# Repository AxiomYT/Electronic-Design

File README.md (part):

# 70cm - 2M Diplexer

* Implements frequency-domain multiplexing. Two input ports (2M, 70CM) are multiplexed onto a third port (OUT)
* the signals on 2M and 70CKM can coexist on OUT port without interfering with each other.
* the signal on 2M Port will occupy the VHF Band and the signal on the 70CM will occupy the UHF band.
* the diplexer consists of a lowpass filter connecting 70CM Port and OUT 
* and a high pass filter connecting 2M Port and OUT.
## PCB

### Topside

### Rearside

## Wiring Diagram

<p>
  <meta http-equiv="content-type" content="text/html; charset=utf-8">
</p>
<p style="margin: 0px; padding: 0px; cursor: text; box-sizing: border-box; counter-reset: list-1 0 list-2 0 list-3 0 list-4 0 list-5 0 list-6 0 list-7 0 list-8 0 list-9 0; color: rgb(49, 49, 49); font-family: Helvetica, Arial, sans-serif; font-size: 13px; font-style: normal; font-variant-ligatures: normal; font-variant-caps: normal; font-weight: 400; letter-spacing: normal; orphans: 2; text-align: left; text-indent: 0px; text-transform: none; white-space: pre-wrap; widows: 2; word-spacing: 0px; -webkit-text-stroke-width: 0px; background-color: rgb(255, 255, 255); text-decoration-style: initial; text-decoration-color: initial;">I needed a small-ish collapsible Yagi-Uda antenna for portable use. Naturally I decided that if I was going to build one, I was going to do it right - the coolest Yagi on the block, the envy of the nearest ham-vention if you will</p>
<p style="margin: 0px; padding: 0px; cursor: text; box-sizing: border-box; counter-reset: list-1 0 list-2 0 list-3 0 list-4 0 list-5 0 list-6 0 list-7 0 list-8 0 list-9 0; color: rgb(49, 49, 49); font-family: Helvetica, Arial, sans-serif; font-size: 13px; font-style: normal; font-variant-ligatures: normal; font-variant-caps: normal; font-weight: 400; letter-spacing: normal; orphans: 2; text-align: left; text-indent: 0px; text-transform: none; white-space: pre-wrap; widows: 2; word-spacing: 0px; -webkit-text-stroke-width: 0px; background-color: rgb(255, 255, 255); text-decoration-style: initial; text-decoration-color: initial;">
  <br style="box-sizing: border-box;">
</p>
<p style="margin: 0px; padding: 0px; cursor: text; box-sizing: border-box; counter-reset: list-1 0 list-2 0 list-3 0 list-4 0 list-5 0 list-6 0 list-7 0 list-8 0 list-9 0; color: rgb(49, 49, 49); font-family: Helvetica, Arial, sans-serif; font-size: 13px; font-style: normal; font-variant-ligatures: normal; font-variant-caps: normal; font-weight: 400; letter-spacing: normal; orphans: 2; text-align: left; text-indent: 0px; text-transform: none; white-space: pre-wrap; widows: 2; word-spacing: 0px; -webkit-text-stroke-width: 0px; background-color: rgb(255, 255, 255); text-decoration-style: initial; text-decoration-color: initial;"><span class="ql-size-huge" style="box-sizing: border-box; font-size: 2.5em;">V/UHF Yagi Diplexer</span></p>
<p style="margin: 0px; padding: 0px; cursor: text; box-sizing: border-box; counter-reset: list-1 0 list-2 0 list-3 0 list-4 0 list-5 0 list-6 0 list-7 0 list-8 0 list-9 0; color: rgb(49, 49, 49); font-family: Helvetica, Arial, sans-serif; font-size: 13px; font-style: normal; font-variant-ligatures: normal; font-variant-caps: normal; font-weight: 400; letter-spacing: normal; orphans: 2; text-align: left; text-indent: 0px; text-transform: none; white-space: pre-wrap; widows: 2; word-spacing: 0px; -webkit-text-stroke-width: 0px; background-color: rgb(255, 255, 255); text-decoration-style: initial; text-decoration-color: initial;">
  <br style="box-sizing: border-box;">
</p>
<p style="margin: 0px; padding: 0px; cursor: text; box-sizing: border-box; counter-reset: list-1 0 list-2 0 list-3 0 list-4 0 list-5 0 list-6 0 list-7 0 list-8 0 list-9 0; color: rgb(49, 49, 49); font-family: Helvetica, Arial, sans-serif; font-size: 13px; font-style: normal; font-variant-ligatures: normal; font-variant-caps: normal; font-weight: 400; letter-spacing: normal; orphans: 2; text-align: left; text-indent: 0px; text-transform: none; white-space: pre-wrap; widows: 2; word-spacing: 0px; -webkit-text-stroke-width: 0px; background-color: rgb(255, 255, 255); text-decoration-style: initial; text-decoration-color: initial;">I came across a project that utilised<em style="font-style: normal; box-sizing: border-box;">&nbsp;carbon fibre</em>, ( the coolest buzz word since blockchain) as a 2 Metre long lightweight boom - accompanied by 3D printed element holders and RG59 Matchingline ( more on that later )</p>
<p style="margin: 0px; padding: 0px; cursor: text; box-sizing: border-box; counter-reset: list-1 0 list-2 0 list-3 0 list-4 0 list-5 0 list-6 0 list-7 0 list-8 0 list-9 0; color: rgb(49, 49, 49); font-family: Helvetica, Arial, sans-serif; font-size: 13px; font-style: normal; font-variant-ligatures: normal; font-variant-caps: normal; font-weight: 400; letter-spacing: normal; orphans: 2; text-align: left; text-indent: 0px; text-transform: none; white-space: pre-wrap; widows: 2; word-spacing: 0px; -webkit-text-stroke-width: 0px; background-color: rgb(255, 255, 255); text-decoration-style: initial; text-decoration-color: initial;">
  <br style="box-sizing: border-box;">
</p>
<p style="margin: 0px; padding: 0px; cursor: text; box-sizing: border-box; counter-reset: list-1 0 list-2 0 list-3 0 list-4 0 list-5 0 list-6 0 list-7 0 list-8 0 list-9 0; color: rgb(49, 49, 49); font-family: Helvetica, Arial, sans-serif; font-size: 13px; font-style: normal; font-variant-ligatures: normal; font-variant-caps: normal; font-weight: 400; letter-spacing: normal; orphans: 2; text-align: left; text-indent: 0px; text-transform: none; white-space: pre-wrap; widows: 2; word-spacing: 0px; -webkit-text-stroke-width: 0px; background-color: rgb(255, 255, 255); text-decoration-style: initial; text-decoration-color: initial;">This project was hosted on Tysonpower.de (
  <a href="https://tysonpower.de/blog/carbon-arrow-yagi-antenna" style="text-decoration: underline; color: rgb(0, 102, 204); transition: color 0.25s ease-out 0s; box-sizing: border-box;" target="_blank">https://tysonpower.de/blog/carbon-arrow-yagi-antenna</a>)
</p>
<p style="margin: 0px; padding: 0px; cursor: text; box-sizing: border-box; counter-reset: list-1 0 list-2 0 list-3 0 list-4 0 list-5 0 list-6 0 list-7 0 list-8 0 list-9 0; color: rgb(49, 49, 49); font-family: Helvetica, Arial, sans-serif; font-size: 13px; font-style: normal; font-variant-ligatures: normal; font-variant-caps: normal; font-weight: 400; letter-spacing: normal; orphans: 2; text-align: left; text-indent: 0px; text-transform: none; white-space: pre-wrap; widows: 2; word-spacing: 0px; -webkit-text-stroke-width: 0px; background-color: rgb(255, 255, 255); text-decoration-style: initial; text-decoration-color: initial;">
  <br style="box-sizing: border-box;">
</p>
<p style="margin: 0px; padding: 0px; cursor: text; box-sizing: border-box; counter-reset: list-1 0 list-2 0 list-3 0 list-4 0 list-5 0 list-6 0 list-7 0 list-8 0 list-9 0; color: rgb(49, 49, 49); font-family: Helvetica, Arial, sans-serif; font-size: 13px; font-style: normal; font-variant-ligatures: normal; font-variant-caps: normal; font-weight: 400; letter-spacing: normal; orphans: 2; text-align: left; text-indent: 0px; text-transform: none; white-space: pre-wrap; widows: 2; word-spacing: 0px; -webkit-text-stroke-width: 0px; background-color: rgb(255, 255, 255); text-decoration-style: initial; text-decoration-color: initial;"><span style="box-sizing: border-box; color: rgb(0, 0, 0);">The Antenna has enough gain for use with a low power 5w handheld radio and is relatively light. This makes it perfect for my use case</span></p>
<p style="margin: 0px; padding: 0px; cursor: text; box-sizing: border-box; counter-reset: list-1 0 list-2 0 list-3 0 list-4 0 list-5 0 list-6 0 list-7 0 list-8 0 list-9 0; color: rgb(49, 49, 49); font-family: Helvetica, Arial, sans-serif; font-size: 13px; font-style: normal; font-variant-ligatures: normal; font-variant-caps: normal; font-weight: 400; letter-spacing: normal; orphans: 2; text-align: left; text-indent: 0px; text-transform: none; white-space: pre-wrap; widows: 2; word-spacing: 0px; -webkit-text-stroke-width: 0px; background-color: rgb(255, 255, 255); text-decoration-style: initial; text-decoration-color: initial;">
  <br style="box-sizing: border-box;">
</p>
<p style="margin: 0px; padding: 0px; cursor: text; box-sizing: border-box; counter-reset: list-1 0 list-2 0 list-3 0 list-4 0 list-5 0 list-6 0 list-7 0 list-8 0 list-9 0; color: rgb(49, 49, 49); font-family: Helvetica, Arial, sans-serif; font-size: 13px; font-style: normal; font-variant-ligatures: normal; font-variant-caps: normal; font-weight: 400; letter-spacing: normal; orphans: 2; text-align: left; text-indent: 0px; text-transform: none; white-space: pre-wrap; widows: 2; word-spacing: 0px; -webkit-text-stroke-width: 0px; background-color: rgb(255, 255, 255); text-decoration-style: initial; text-decoration-color: initial;"><strong style="box-sizing: border-box;">Material list</strong></p>
<p style="margin: 0px; padding: 0px; cursor: text; box-sizing: border-box; counter-reset: list-1 0 list-2 0 list-3 0 list-4 0 list-5 0 list-6 0 list-7 0 list-8 0 list-9 0; color: rgb(49, 49, 49); font-family: Helvetica, Arial, sans-serif; font-size: 13px; font-style: normal; font-variant-ligatures: normal; font-variant-caps: normal; font-weight: 400; letter-spacing: normal; orphans: 2; text-align: left; text-indent: 0px; text-transform: none; white-space: pre-wrap; widows: 2; word-spacing: 0px; -webkit-text-stroke-width: 0px; background-color: rgb(255, 255, 255); text-decoration-style: initial; text-decoration-color: initial;">
  <br style="box-sizing: border-box;">
</p>
<ul style="margin: 0px; padding: 0px 0px 0px 1.5em; list-style: none outside none; cursor: text; box-sizing: border-box; counter-reset: list-1 0 list-2 0 list-3 0 list-4 0 list-5 0 list-6 0 list-7 0 list-8 0 list-9 0; color: rgb(49, 49, 49); font-family: Helvetica, Arial, sans-serif; font-size: 13px; font-style: normal; font-variant-ligatures: normal; font-variant-caps: normal; font-weight: 400; letter-spacing: normal; orphans: 2; text-align: left; text-indent: 0px; text-transform: none; white-space: pre-wrap; widows: 2; word-spacing: 0px; -webkit-text-stroke-width: 0px; background-color: rgb(255, 255, 255); text-decoration-style: initial; text-decoration-color: initial;">
  <li style="margin: 0px; padding: 0px 0px 0px 1.5em; list-style: none outside none; box-sizing: border-box;">2x 50cm carbon rod - 12mm outer diameter (boom)</li>
  <li style="margin: 0px; padding: 0px 0px 0px 1.5em; list-style: none outside none; box-sizing: border-box;">Aluminium clamps for the carbon rods</li>
  <li style="margin: 0px; padding: 0px 0px 0px 1.5em; list-style: none outside none; box-sizing: border-box;">some m3 bolts and nuts</li>
  <li style="margin: 0px; padding: 0px 0px 0px 1.5em; list-style: none outside none; box-sizing: border-box;">3D printed parts - 
    <a href="https://www.thingiverse.com/thing:3289189" style="text-decoration: underline; color: rgb(0, 102, 204); transition: color 0.25s ease-out 0s; box-sizing: border-box;" target="_blank">https://www.thingiverse.com/thing:3289189</a>
  </li>
  <li style="margin: 0px; padding: 0px 0px 0px 1.5em; list-style: none outside none; box-sizing: border-box;">Aluminium rods with 6mm (~3,5m) and 10mm (~1,5m) diameter (Elements)</li>
  <li style="margin: 0px; padding: 0px 0px 0px 1.5em; list-style: none outside none; box-sizing: border-box;">50Ohm [ RG58/U ] and 75Ohm cable [ RG59 ] (at least two metres of each)</li>
  <li style="margin: 0px; padding: 0px 0px 0px 1.5em; list-style: none outside none; box-sizing: border-box;">Cable lugs (for m3 screws)</li>
</ul>
<p style="margin: 0px; padding: 0px; cursor: text; box-sizing: border-box; counter-reset: list-1 0 list-2 0 list-3 0 list-4 0 list-5 0 list-6 0 list-7 0 list-8 0 list-9 0; color: rgb(49, 49, 49); font-family: Helvetica, Arial, sans-serif; font-size: 13px; font-style: normal; font-variant-ligatures: normal; font-variant-caps: normal; font-weight: 400; letter-spacing: normal; orphans: 2; text-align: left; text-indent: 0px; text-transform: none; white-space: pre-wrap; widows: 2; word-spacing: 0px; -webkit-text-stroke-width: 0px; background-color: rgb(255, 255, 255); text-decoration-style: initial; text-decoration-color: initial;">
  <br style="box-sizing: border-box;">
</p>
<p style="margin: 0px; padding: 0px; cursor: text; box-sizing: border-box; counter-reset: list-1 0 list-2 0 list-3 0 list-4 0 list-5 0 list-6 0 list-7 0 list-8 0 list-9 0; color: rgb(49, 49, 49); font-family: Helvetica, Arial, sans-serif; font-size: 13px; font-style: normal; font-variant-ligatures: normal; font-variant-caps: normal; font-weight: 400; letter-spacing: normal; orphans: 2; text-align: left; text-indent: 0px; text-transform: none; white-space: pre-wrap; widows: 2; word-spacing: 0px; -webkit-text-stroke-width: 0px; background-color: rgb(255, 255, 255); text-decoration-style: initial; text-decoration-color: initial;"><span style="box-sizing: border-box; color: rgb(0, 0, 0);">The parts have to be spaced according to the image below to get the right spacing between the elements. Note that the 2m and 70cm yagi are crossed by 90°.</span></p>
<p style="margin: 0px; padding: 0px; cursor: text; box-sizing: border-box; counter-reset: list-1 0 list-2 0 list-3 0 list-4 0 list-5 0 list-6 0 list-7 0 list-8 0 list-9 0; color: rgb(49, 49, 49); font-family: Helvetica, Arial, sans-serif; font-size: 13px; font-style: normal; font-variant-ligatures: normal; font-variant-caps: normal; font-weight: 400; letter-spacing: normal; orphans: 2; text-align: left; text-indent: 0px; text-transform: none; white-space: pre-wrap; widows: 2; word-spacing: 0px; -webkit-text-stroke-width: 0px; background-color: rgb(255, 255, 255); text-decoration-style: initial; text-decoration-color: initial;">
  <br style="box-sizing: border-box;">
</p>
<p style="margin: 0px; padding: 0px; cursor: text; box-sizing: border-box; counter-reset: list-1 0 list-2 0 list-3 0 list-4 0 list-5 0 list-6 0 list-7 0 list-8 0 list-9 0; color: rgb(49, 49, 49); font-family: Helvetica, Arial, sans-serif; font-size: 13px; font-style: normal; font-variant-ligatures: normal; font-variant-caps: normal; font-weight: 400; letter-spacing: normal; orphans: 2; text-align: left; text-indent: 0px; text-transform: none; white-space: pre-wrap; widows: 2; word-spacing: 0px; -webkit-text-stroke-width: 0px; background-color: rgb(255, 255, 255); text-decoration-style: initial; text-decoration-color: initial;">
  
</p>
<p style="margin: 0px; padding: 0px; cursor: text; box-sizing: border-box; counter-reset: list-1 0 list-2 0 list-3 0 list-4 0 list-5 0 list-6 0 list-7 0 list-8 0 list-9 0; color: rgb(49, 49, 49); font-family: Helvetica, Arial, sans-serif; font-size: 13px; font-style: normal; font-variant-ligatures: normal; font-variant-caps: normal; font-weight: 400; letter-spacing: normal; orphans: 2; text-align: left; text-indent: 0px; text-transform: none; white-space: pre-wrap; widows: 2; word-spacing: 0px; -webkit-text-stroke-width: 0px; background-color: rgb(255, 255, 255); text-decoration-style: initial; text-decoration-color: initial;">
  <br style="box-sizing: border-box;">
</p>
<p style="margin: 0px; padding: 0px; cursor: text; box-sizing: border-box; counter-reset: list-1 0 list-2 0 list-3 0 list-4 0 list-5 0 list-6 0 list-7 0 list-8 0 list-9 0; color: rgb(49, 49, 49); font-family: Helvetica, Arial, sans-serif; font-size: 13px; font-style: normal; font-variant-ligatures: normal; font-variant-caps: normal; font-weight: 400; letter-spacing: normal; orphans: 2; text-align: left; text-indent: 0px; text-transform: none; white-space: pre-wrap; widows: 2; word-spacing: 0px; -webkit-text-stroke-width: 0px; background-color: rgb(255, 255, 255); text-decoration-style: initial; text-decoration-color: initial;"><span style="box-sizing: border-box; color: rgb(0, 0, 0);">The Elements need to have the following lengths and need to be mounted centred on the boom.</span></p>
<p style="margin: 0px; padding: 0px; cursor: text; box-sizing: border-box; counter-reset: list-1 0 list-2 0 list-3 0 list-4 0 list-5 0 list-6 0 list-7 0 list-8 0 list-9 0; color: rgb(49, 49, 49); font-family: Helvetica, Arial, sans-serif; font-size: 13px; font-style: normal; font-variant-ligatures: normal; font-variant-caps: normal; font-weight: 400; letter-spacing: normal; orphans: 2; text-align: left; text-indent: 0px; text-transform: none; white-space: pre-wrap; widows: 2; word-spacing: 0px; -webkit-text-stroke-width: 0px; background-color: rgb(255, 255, 255); text-decoration-style: initial; text-decoration-color: initial;">
  <br style="box-sizing: border-box;">
</p>
<p style="margin: 0px; padding: 0px; cursor: text; box-sizing: border-box; counter-reset: list-1 0 list-2 0 list-3 0 list-4 0 list-5 0 list-6 0 list-7 0 list-8 0 list-9 0; color: rgb(49, 49, 49); font-family: Helvetica, Arial, sans-serif; font-size: 13px; font-style: normal; font-variant-ligatures: normal; font-variant-caps: normal; font-weight: 400; letter-spacing: normal; orphans: 2; text-align: left; text-indent: 0px; text-transform: none; white-space: pre-wrap; widows: 2; word-spacing: 0px; -webkit-text-stroke-width: 0px; background-color: rgb(255, 255, 255); text-decoration-style: initial; text-decoration-color: initial;">
  
</p>
<p style="margin: 0px; padding: 0px; cursor: text; box-sizing: border-box; counter-reset: list-1 0 list-2 0 list-3 0 list-4 0 list-5 0 list-6 0 list-7 0 list-8 0 list-9 0; color: rgb(49, 49, 49); font-family: Helvetica, Arial, sans-serif; font-size: 13px; font-style: normal; font-variant-ligatures: normal; font-variant-caps: normal; font-weight: 400; letter-spacing: normal; orphans: 2; text-align: left; text-indent: 0px; text-transform: none; white-space: pre-wrap; widows: 2; word-spacing: 0px; -webkit-text-stroke-width: 0px; background-color: rgb(255, 255, 255); text-decoration-style: initial; text-decoration-color: initial;">
  <br style="box-sizing: border-box;">
</p>
<p style="margin: 0px; padding: 0px; cursor: text; box-sizing: border-box; counter-reset: list-1 0 list-2 0 list-3 0 list-4 0 list-5 0 list-6 0 list-7 0 list-8 0 list-9 0; color: rgb(49, 49, 49); font-family: Helvetica, Arial, sans-serif; font-size: 13px; font-style: normal; font-variant-ligatures: normal; font-variant-caps: normal; font-weight: 400; letter-spacing: normal; orphans: 2; text-align: left; text-indent: 0px; text-transform: none; white-space: pre-wrap; widows: 2; word-spacing: 0px; -webkit-text-stroke-width: 0px; background-color: rgb(255, 255, 255); text-decoration-style: initial; text-decoration-color: initial;">
  
</p>
<p style="margin: 0px; padding: 0px; cursor: text; box-sizing: border-box; counter-reset: list-1 0 list-2 0 list-3 0 list-4 0 list-5 0 list-6 0 list-7 0 list-8 0 list-9 0; color: rgb(49, 49, 49); font-family: Helvetica, Arial, sans-serif; font-size: 13px; font-style: normal; font-variant-ligatures: normal; font-variant-caps: normal; font-weight: 400; letter-spacing: normal; orphans: 2; text-align: left; text-indent: 0px; text-transform: none; white-space: pre-wrap; widows: 2; word-spacing: 0px; -webkit-text-stroke-width: 0px; background-color: rgb(255, 255, 255); text-decoration-style: initial; text-decoration-color: initial;">
  <br style="box-sizing: border-box;">
</p>
<p style="margin: 0px; padding: 0px; cursor: text; box-sizing: border-box; counter-reset: list-1 0 list-2 0 list-3 0 list-4 0 list-5 0 list-6 0 list-7 0 list-8 0 list-9 0; color: rgb(49, 49, 49); font-family: Helvetica, Arial, sans-serif; font-size: 13px; font-style: normal; font-variant-ligatures: normal; font-variant-caps: normal; font-weight: 400; letter-spacing: normal; orphans: 2; text-align: left; text-indent: 0px; text-transform: none; white-space: pre-wrap; widows: 2; word-spacing: 0px; -webkit-text-stroke-width: 0px; background-color: rgb(255, 255, 255); text-decoration-style: initial; text-decoration-color: initial;">
  <br style="box-sizing: border-box;">
</p>
<p style="margin: 0px; padding: 0px; cursor: text; box-sizing: border-box; counter-reset: list-1 0 list-2 0 list-3 0 list-4 0 list-5 0 list-6 0 list-7 0 list-8 0 list-9 0; color: rgb(49, 49, 49); font-family: Helvetica, Arial, sans-serif; font-size: 13px; font-style: normal; font-variant-ligatures: normal; font-variant-caps: normal; font-weight: 400; letter-spacing: normal; orphans: 2; text-align: left; text-indent: 0px; text-transform: none; white-space: pre-wrap; widows: 2; word-spacing: 0px; -webkit-text-stroke-width: 0px; background-color: rgb(255, 255, 255); text-decoration-style: initial; text-decoration-color: initial;"><strong class="ql-size-large" style="box-sizing: border-box; font-size: 1.5em;">Note on Matchingline / RF Magic</strong></p>
<p style="margin: 0px; padding: 0px; cursor: text; box-sizing: border-box; counter-reset: list-1 0 list-2 0 list-3 0 list-4 0 list-5 0 list-6 0 list-7 0 list-8 0 list-9 0; color: rgb(49, 49, 49); font-family: Helvetica, Arial, sans-serif; font-size: 13px; font-style: normal; font-variant-ligatures: normal; font-variant-caps: normal; font-weight: 400; letter-spacing: normal; orphans: 2; text-align: left; text-indent: 0px; text-transform: none; white-space: pre-wrap; widows: 2; word-spacing: 0px; -webkit-text-stroke-width: 0px; background-color: rgb(255, 255, 255); text-decoration-style: initial; text-decoration-color: initial;">
  <br style="box-sizing: border-box;">
</p>
<p style="margin: 0px; padding: 0px; cursor: text; box-sizing: border-box; counter-reset: list-1 0 list-2 0 list-3 0 list-4 0 list-5 0 list-6 0 list-7 0 list-8 0 list-9 0; color: rgb(49, 49, 49); font-family: Helvetica, Arial, sans-serif; font-size: 13px; font-style: normal; font-variant-ligatures: normal; font-variant-caps: normal; font-weight: 400; letter-spacing: normal; orphans: 2; text-align: left; text-indent: 0px; text-transform: none; white-space: pre-wrap; widows: 2; word-spacing: 0px; -webkit-text-stroke-width: 0px; background-color: rgb(255, 255, 255); text-decoration-style: initial; text-decoration-color: initial;">So you might have noticed I mentioned 75Ohm Cable ( 2 Metres of the stuff )</p>
<p style="margin: 0px; padding: 0px; cursor: text; box-sizing: border-box; counter-reset: list-1 0 list-2 0 list-3 0 list-4 0 list-5 0 list-6 0 list-7 0 list-8 0 list-9 0; color: rgb(49, 49, 49); font-family: Helvetica, Arial, sans-serif; font-size: 13px; font-style: normal; font-variant-ligatures: normal; font-variant-caps: normal; font-weight: 400; letter-spacing: normal; orphans: 2; text-align: left; text-indent: 0px; text-transform: none; white-space: pre-wrap; widows: 2; word-spacing: 0px; -webkit-text-stroke-width: 0px; background-color: rgb(255, 255, 255); text-decoration-style: initial; text-decoration-color: initial;">
  <br style="box-sizing: border-box;">
</p>
<p style="margin: 0px; padding: 0px; cursor: text; box-sizing: border-box; counter-reset: list-1 0 list-2 0 list-3 0 list-4 0 list-5 0 list-6 0 list-7 0 list-8 0 list-9 0; color: rgb(49, 49, 49); font-family: Helvetica, Arial, sans-serif; font-size: 13px; font-style: normal; font-variant-ligatures: normal; font-variant-caps: normal; font-weight: 400; letter-spacing: normal; orphans: 2; text-align: left; text-indent: 0px; text-transform: none; white-space: pre-wrap; widows: 2; word-spacing: 0px; -webkit-text-stroke-width: 0px; background-color: rgb(255, 255, 255); text-decoration-style: initial; text-decoration-color: initial;">Your first step is to make a matchingline that is made out of two pieces of RG59 Concatenated and parallel to one another</p>
<p style="margin: 0px; padding: 0px; cursor: text; box-sizing: border-box; counter-reset: list-1 0 list-2 0 list-3 0 list-4 0 list-5 0 list-6 0 list-7 0 list-8 0 list-9 0; color: rgb(49, 49, 49); font-family: Helvetica, Arial, sans-serif; font-size: 13px; font-style: normal; font-variant-ligatures: normal; font-variant-caps: normal; font-weight: 400; letter-spacing: normal; orphans: 2; text-align: left; text-indent: 0px; text-transform: none; white-space: pre-wrap; widows: 2; word-spacing: 0px; -webkit-text-stroke-width: 0px; background-color: rgb(255, 255, 255); text-decoration-style: initial; text-decoration-color: initial;">
  <br style="box-sizing: border-box;">
</p>
<p style="margin: 0px; padding: 0px; cursor: text; box-sizing: border-box; counter-reset: list-1 0 list-2 0 list-3 0 list-4 0 list-5 0 list-6 0 list-7 0 list-8 0 list-9 0; color: rgb(49, 49, 49); font-family: Helvetica, Arial, sans-serif; font-size: 13px; font-style: normal; font-variant-ligatures: normal; font-variant-caps: normal; font-weight: 400; letter-spacing: normal; orphans: 2; text-align: left; text-indent: 0px; text-transform: none; white-space: pre-wrap; widows: 2; word-spacing: 0px; -webkit-text-stroke-width: 0px; background-color: rgb(255, 255, 255); text-decoration-style: initial; text-decoration-color: initial;">You will need two of these Cable harnesses -&nbsp;</p>
<p style="margin: 0px; padding: 0px; cursor: text; box-sizing: border-box; counter-reset: list-1 0 list-2 0 list-3 0 list-4 0 list-5 0 list-6 0 list-7 0 list-8 0 list-9 0; color: rgb(49, 49, 49); font-family: Helvetica, Arial, sans-serif; font-size: 13px; font-style: normal; font-variant-ligatures: normal; font-variant-caps: normal; font-weight: 400; letter-spacing: normal; orphans: 2; text-align: left; text-indent: 0px; text-transform: none; white-space: pre-wrap; widows: 2; word-spacing: 0px; -webkit-text-stroke-width: 0px; background-color: rgb(255, 255, 255); text-decoration-style: initial; text-decoration-color: initial;">one for the 2M Triple Element and one for the 70CM Penta-element</p>
<p style="margin: 0px; padding: 0px; cursor: text; box-sizing: border-box; counter-reset: list-1 0 list-2 0 list-3 0 list-4 0 list-5 0 list-6 0 list-7 0 list-8 0 list-9 0; color: rgb(49, 49, 49); font-family: Helvetica, Arial, sans-serif; font-size: 13px; font-style: normal; font-variant-ligatures: normal; font-variant-caps: normal; font-weight: 400; letter-spacing: normal; orphans: 2; text-align: left; text-indent: 0px; text-transform: none; white-space: pre-wrap; widows: 2; word-spacing: 0px; -webkit-text-stroke-width: 0px; background-color: rgb(255, 255, 255); text-decoration-style: initial; text-decoration-color: initial;">The length of the insulated part of the cable for the 2M band is 343mm and 115mm for the 70CM band</p>
<p style="margin: 0px; padding: 0px; cursor: text; box-sizing: border-box; counter-reset: list-1 0 list-2 0 list-3 0 list-4 0 list-5 0 list-6 0 list-7 0 list-8 0 list-9 0; color: rgb(49, 49, 49); font-family: Helvetica, Arial, sans-serif; font-size: 13px; font-style: normal; font-variant-ligatures: normal; font-variant-caps: normal; font-weight: 400; letter-spacing: normal; orphans: 2; text-align: left; text-indent: 0px; text-transform: none; white-space: pre-wrap; widows: 2; word-spacing: 0px; -webkit-text-stroke-width: 0px; background-color: rgb(255, 255, 255); text-decoration-style: initial; text-decoration-color: initial;">
  <br style="box-sizing: border-box;">
</p>
<p style="margin: 0px; padding: 0px; cursor: text; box-sizing: border-box; counter-reset: list-1 0 list-2 0 list-3 0 list-4 0 list-5 0 list-6 0 list-7 0 list-8 0 list-9 0; color: rgb(49, 49, 49); font-family: Helvetica, Arial, sans-serif; font-size: 13px; font-style: normal; font-variant-ligatures: normal; font-variant-caps: normal; font-weight: 400; letter-spacing: normal; orphans: 2; text-align: left; text-indent: 0px; text-transform: none; white-space: pre-wrap; widows: 2; word-spacing: 0px; -webkit-text-stroke-width: 0px; background-color: rgb(255, 255, 255); text-decoration-style: initial; text-decoration-color: initial;">I made sure that both stay parallel by using some isolating tape</p>
<p style="margin: 0px; padding: 0px; cursor: text; box-sizing: border-box; counter-reset: list-1 0 list-2 0 list-3 0 list-4 0 list-5 0 list-6 0 list-7 0 list-8 0 list-9 0; color: rgb(49, 49, 49); font-family: Helvetica, Arial, sans-serif; font-size: 13px; font-style: normal; font-variant-ligatures: normal; font-variant-caps: normal; font-weight: 400; letter-spacing: normal; orphans: 2; text-align: left; text-indent: 0px; text-transform: none; white-space: pre-wrap; widows: 2; word-spacing: 0px; -webkit-text-stroke-width: 0px; background-color: rgb(255, 255, 255); text-decoration-style: initial; text-decoration-color: initial;">To finish the cable - solder both the centre conductors together and the outer braiding of both parallel cables so you have one single signal and one single outer sheath connection on both sides.</p>
<p style="margin: 0px; padding: 0px; cursor: text; box-sizing: border-box; counter-reset: list-1 0 list-2 0 list-3 0 list-4 0 list-5 0 list-6 0 list-7 0 list-8 0 list-9 0; color: rgb(49, 49, 49); font-family: Helvetica, Arial, sans-serif; font-size: 13px; font-style: normal; font-variant-ligatures: normal; font-variant-caps: normal; font-weight: 400; letter-spacing: normal; orphans: 2; text-align: left; text-indent: 0px; text-transform: none; white-space: pre-wrap; widows: 2; word-spacing: 0px; -webkit-text-stroke-width: 0px; background-color: rgb(255, 255, 255); text-decoration-style: initial; text-decoration-color: initial;">
  <br style="box-sizing: border-box;">
</p>
<p style="margin: 0px; padding: 0px; cursor: text; box-sizing: border-box; counter-reset: list-1 0 list-2 0 list-3 0 list-4 0 list-5 0 list-6 0 list-7 0 list-8 0 list-9 0; color: rgb(49, 49, 49); font-family: Helvetica, Arial, sans-serif; font-size: 13px; font-style: normal; font-variant-ligatures: normal; font-variant-caps: normal; font-weight: 400; letter-spacing: normal; orphans: 2; text-align: left; text-indent: 0px; text-transform: none; white-space: pre-wrap; widows: 2; word-spacing: 0px; -webkit-text-stroke-width: 0px; background-color: rgb(255, 255, 255); text-decoration-style: initial; text-decoration-color: initial;">
  
</p>
<p style="margin: 0px; padding: 0px; cursor: text; box-sizing: border-box; counter-reset: list-1 0 list-2 0 list-3 0 list-4 0 list-5 0 list-6 0 list-7 0 list-8 0 list-9 0; color: rgb(49, 49, 49); font-family: Helvetica, Arial, sans-serif; font-size: 13px; font-style: normal; font-variant-ligatures: normal; font-variant-caps: normal; font-weight: 400; letter-spacing: normal; orphans: 2; text-align: left; text-indent: 0px; text-transform: none; white-space: pre-wrap; widows: 2; word-spacing: 0px; -webkit-text-stroke-width: 0px; background-color: rgb(255, 255, 255); text-decoration-style: initial; text-decoration-color: initial;">
  <br style="box-sizing: border-box;">
</p>
<p style="margin: 0px; padding: 0px; cursor: text; box-sizing: border-box; counter-reset: list-1 0 list-2 0 list-3 0 list-4 0 list-5 0 list-6 0 list-7 0 list-8 0 list-9 0; color: rgb(49, 49, 49); font-family: Helvetica, Arial, sans-serif; font-size: 13px; font-style: normal; font-variant-ligatures: normal; font-variant-caps: normal; font-weight: 400; letter-spacing: normal; orphans: 2; text-align: left; text-indent: 0px; text-transform: none; white-space: pre-wrap; widows: 2; word-spacing: 0px; -webkit-text-stroke-width: 0px; background-color: rgb(255, 255, 255); text-decoration-style: initial; text-decoration-color: initial;">For the output cable, use regular old RG58/U with your preferred termination (SMA / BNC)</p>
<p style="margin: 0px; padding: 0px; cursor: text; box-sizing: border-box; counter-reset: list-1 0 list-2 0 list-3 0 list-4 0 list-5 0 list-6 0 list-7 0 list-8 0 list-9 0; color: rgb(49, 49, 49); font-family: Helvetica, Arial, sans-serif; font-size: 13px; font-style: normal; font-variant-ligatures: normal; font-variant-caps: normal; font-weight: 400; letter-spacing: normal; orphans: 2; text-align: left; text-indent: 0px; text-transform: none; white-space: pre-wrap; widows: 2; word-spacing: 0px; -webkit-text-stroke-width: 0px; background-color: rgb(255, 255, 255); text-decoration-style: initial; text-decoration-color: initial;">
  <br style="box-sizing: border-box;">
</p>
<p style="margin: 0px; padding: 0px; cursor: text; box-sizing: border-box; counter-reset: list-1 0 list-2 0 list-3 0 list-4 0 list-5 0 list-6 0 list-7 0 list-8 0 list-9 0; color: rgb(49, 49, 49); font-family: Helvetica, Arial, sans-serif; font-size: 13px; font-style: normal; font-variant-ligatures: normal; font-variant-caps: normal; font-weight: 400; letter-spacing: normal; orphans: 2; text-align: left; text-indent: 0px; text-transform: none; white-space: pre-wrap; widows: 2; word-spacing: 0px; -webkit-text-stroke-width: 0px; background-color: rgb(255, 255, 255); text-decoration-style: initial; text-decoration-color: initial;">To connect to the elements to the feed point - I used Cable Lugs that get attached to the aluminium with screws.</p>
<p style="margin: 0px; padding: 0px; cursor: text; box-sizing: border-box; counter-reset: list-1 0 list-2 0 list-3 0 list-4 0 list-5 0 list-6 0 list-7 0 list-8 0 list-9 0; color: rgb(49, 49, 49); font-family: Helvetica, Arial, sans-serif; font-size: 13px; font-style: normal; font-variant-ligatures: normal; font-variant-caps: normal; font-weight: 400; letter-spacing: normal; orphans: 2; text-align: left; text-indent: 0px; text-transform: none; white-space: pre-wrap; widows: 2; word-spacing: 0px; -webkit-text-stroke-width: 0px; background-color: rgb(255, 255, 255); text-decoration-style: initial; text-decoration-color: initial;">
  <br style="box-sizing: border-box;">
</p>
<p style="margin: 0px; padding: 0px; cursor: text; box-sizing: border-box; counter-reset: list-1 0 list-2 0 list-3 0 list-4 0 list-5 0 list-6 0 list-7 0 list-8 0 list-9 0; color: rgb(49, 49, 49); font-family: Helvetica, Arial, sans-serif; font-size: 13px; font-style: normal; font-variant-ligatures: normal; font-variant-caps: normal; font-weight: 400; letter-spacing: normal; orphans: 2; text-align: left; text-indent: 0px; text-transform: none; white-space: pre-wrap; widows: 2; word-spacing: 0px; -webkit-text-stroke-width: 0px; background-color: rgb(255, 255, 255); text-decoration-style: initial; text-decoration-color: initial;">
  
</p>
<p style="margin: 0px; padding: 0px; cursor: text; box-sizing: border-box; counter-reset: list-1 0 list-2 0 list-3 0 list-4 0 list-5 0 list-6 0 list-7 0 list-8 0 list-9 0; color: rgb(49, 49, 49); font-family: Helvetica, Arial, sans-serif; font-size: 13px; font-style: normal; font-variant-ligatures: normal; font-variant-caps: normal; font-weight: 400; letter-spacing: normal; orphans: 2; text-align: left; text-indent: 0px; text-transform: none; white-space: pre-wrap; widows: 2; word-spacing: 0px; -webkit-text-stroke-width: 0px; background-color: rgb(255, 255, 255); text-decoration-style: initial; text-decoration-color: initial;">
  <br style="box-sizing: border-box;">
</p>
<p style="margin: 0px; padding: 0px; cursor: text; box-sizing: border-box; counter-reset: list-1 0 list-2 0 list-3 0 list-4 0 list-5 0 list-6 0 list-7 0 list-8 0 list-9 0; color: rgb(49, 49, 49); font-family: Helvetica, Arial, sans-serif; font-size: 13px; font-style: normal; font-variant-ligatures: normal; font-variant-caps: normal; font-weight: 400; letter-spacing: normal; orphans: 2; text-align: left; text-indent: 0px; text-transform: none; white-space: pre-wrap; widows: 2; word-spacing: 0px; -webkit-text-stroke-width: 0px; background-color: rgb(255, 255, 255); text-decoration-style: initial; text-decoration-color: initial;">
  <br style="box-sizing: border-box;">
</p>
<p style="margin: 0px; padding: 0px; cursor: text; box-sizing: border-box; counter-reset: list-1 0 list-2 0 list-3 0 list-4 0 list-5 0 list-6 0 list-7 0 list-8 0 list-9 0; color: rgb(49, 49, 49); font-family: Helvetica, Arial, sans-serif; font-size: 13px; font-style: normal; font-variant-ligatures: normal; font-variant-caps: normal; font-weight: 400; letter-spacing: normal; orphans: 2; text-align: left; text-indent: 0px; text-transform: none; white-space: pre-wrap; widows: 2; word-spacing: 0px; -webkit-text-stroke-width: 0px; background-color: rgb(255, 255, 255); text-decoration-style: initial; text-decoration-color: initial;"><strong class="ql-size-huge" style="box-sizing: border-box; font-size: 2.5em;">The PCB</strong></p>
<p style="margin: 0px; padding: 0px; cursor: text; box-sizing: border-box; counter-reset: list-1 0 list-2 0 list-3 0 list-4 0 list-5 0 list-6 0 list-7 0 list-8 0 list-9 0; color: rgb(49, 49, 49); font-family: Helvetica, Arial, sans-serif; font-size: 13px; font-style: normal; font-variant-ligatures: normal; font-variant-caps: normal; font-weight: 400; letter-spacing: normal; orphans: 2; text-align: left; text-indent: 0px; text-transform: none; white-space: pre-wrap; widows: 2; word-spacing: 0px; -webkit-text-stroke-width: 0px; background-color: rgb(255, 255, 255); text-decoration-style: initial; text-decoration-color: initial;">
  <br style="box-sizing: border-box;">
</p>
<p style="margin: 0px; padding: 0px; cursor: text; box-sizing: border-box; counter-reset: list-1 0 list-2 0 list-3 0 list-4 0 list-5 0 list-6 0 list-7 0 list-8 0 list-9 0; color: rgb(49, 49, 49); font-family: Helvetica, Arial, sans-serif; font-size: 13px; font-style: normal; font-variant-ligatures: normal; font-variant-caps: normal; font-weight: 400; letter-spacing: normal; orphans: 2; text-align: left; text-indent: 0px; text-transform: none; white-space: pre-wrap; widows: 2; word-spacing: 0px; -webkit-text-stroke-width: 0px; background-color: rgb(255, 255, 255); text-decoration-style: initial; text-decoration-color: initial;">Onto the reason for this post - The kind folks at PCBway reached out to me to help me print my circuit board design. This is a short outline of what it does!</p>
<p style="margin: 0px; padding: 0px; cursor: text; box-sizing: border-box; counter-reset: list-1 0 list-2 0 list-3 0 list-4 0 list-5 0 list-6 0 list-7 0 list-8 0 list-9 0; color: rgb(49, 49, 49); font-family: Helvetica, Arial, sans-serif; font-size: 13px; font-style: normal; font-variant-ligatures: normal; font-variant-caps: normal; font-weight: 400; letter-spacing: normal; orphans: 2; text-align: left; text-indent: 0px; text-transform: none; white-space: pre-wrap; widows: 2; word-spacing: 0px; -webkit-text-stroke-width: 0px; background-color: rgb(255, 255, 255); text-decoration-style: initial; text-decoration-color: initial;">
  <br style="box-sizing: border-box;">
</p>
<p style="margin: 0px; padding: 0px; cursor: text; box-sizing: border-box; counter-reset: list-1 0 list-2 0 list-3 0 list-4 0 list-5 0 list-6 0 list-7 0 list-8 0 list-9 0; color: rgb(49, 49, 49); font-family: Helvetica, Arial, sans-serif; font-size: 13px; font-style: normal; font-variant-ligatures: normal; font-variant-caps: normal; font-weight: 400; letter-spacing: normal; orphans: 2; text-align: left; text-indent: 0px; text-transform: none; white-space: pre-wrap; widows: 2; word-spacing: 0px; -webkit-text-stroke-width: 0px; background-color: rgb(255, 255, 255); text-decoration-style: initial; text-decoration-color: initial;">Because I only wanted one output to my radio - I added a diplexer, or otherwise known as RF Magic..for those interested - this is the theory behind diplexers</p>
<p style="margin: 0px; padding: 0px; cursor: text; box-sizing: border-box; counter-reset: list-1 0 list-2 0 list-3 0 list-4 0 list-5 0 list-6 0 list-7 0 list-8 0 list-9 0; color: rgb(49, 49, 49); font-family: Helvetica, Arial, sans-serif; font-size: 13px; font-style: normal; font-variant-ligatures: normal; font-variant-caps: normal; font-weight: 400; letter-spacing: normal; orphans: 2; text-align: left; text-indent: 0px; text-transform: none; white-space: pre-wrap; widows: 2; word-spacing: 0px; -webkit-text-stroke-width: 0px; background-color: rgb(255, 255, 255); text-decoration-style: initial; text-decoration-color: initial;">
  <br style="box-sizing: border-box;">
</p>
<ul style="margin: 0px; padding: 0px 0px 0px 1.5em; list-style: none outside none; cursor: text; box-sizing: border-box; counter-reset: list-1 0 list-2 0 list-3 0 list-4 0 list-5 0 list-6 0 list-7 0 list-8 0 list-9 0; color: rgb(49, 49, 49); font-family: Helvetica, Arial, sans-serif; font-size: 13px; font-style: normal; font-variant-ligatures: normal; font-variant-caps: normal; font-weight: 400; letter-spacing: normal; orphans: 2; text-align: left; text-indent: 0px; text-transform: none; white-space: pre-wrap; widows: 2; word-spacing: 0px; -webkit-text-stroke-width: 0px; background-color: rgb(255, 255, 255); text-decoration-style: initial; text-decoration-color: initial;">
  <li style="margin: 0px; padding: 0px 0px 0px 1.5em; list-style: none outside none; box-sizing: border-box;">Implements frequency-domain multiplexing. Two input ports (2M, 70CM) are multiplexed onto a third port (OUT)</li>
  <li style="margin: 0px; padding: 0px 0px 0px 1.5em; list-style: none outside none; box-sizing: border-box;">the signals on 2M and 70CM can coexist on OUT port without interfering with each other.</li>
  <li style="margin: 0px; padding: 0px 0px 0px 1.5em; list-style: none outside none; box-sizing: border-box;">the signal on 2M Port will occupy the VHF Band and the signal on the 70CM will occupy the UHF band.</li>
  <li style="margin: 0px; padding: 0px 0px 0px 1.5em; list-style: none outside none; box-sizing: border-box;">the diplexer consists of a lowpass filter connecting 70CM Port and OUT</li>
  <li style="margin: 0px; padding: 0px 0px 0px 1.5em; list-style: none outside none; box-sizing: border-box;">and a high pass filter connecting 2M Port and OUT.</li>
</ul>
<p style="margin: 0px; padding: 0px; cursor: text; box-sizing: border-box; counter-reset: list-1 0 list-2 0 list-3 0 list-4 0 list-5 0 list-6 0 list-7 0 list-8 0 list-9 0; color: rgb(49, 49, 49); font-family: Helvetica, Arial, sans-serif; font-size: 13px; font-style: normal; font-variant-ligatures: normal; font-variant-caps: normal; font-weight: 400; letter-spacing: normal; orphans: 2; text-align: left; text-indent: 0px; text-transform: none; white-space: pre-wrap; widows: 2; word-spacing: 0px; -webkit-text-stroke-width: 0px; background-color: rgb(255, 255, 255); text-decoration-style: initial; text-decoration-color: initial;">
  <br style="box-sizing: border-box;">
</p>
<p style="margin: 0px; padding: 0px; cursor: text; box-sizing: border-box; counter-reset: list-1 0 list-2 0 list-3 0 list-4 0 list-5 0 list-6 0 list-7 0 list-8 0 list-9 0; color: rgb(49, 49, 49); font-family: Helvetica, Arial, sans-serif; font-size: 13px; font-style: normal; font-variant-ligatures: normal; font-variant-caps: normal; font-weight: 400; letter-spacing: normal; orphans: 2; text-align: left; text-indent: 0px; text-transform: none; white-space: pre-wrap; widows: 2; word-spacing: 0px; -webkit-text-stroke-width: 0px; background-color: rgb(255, 255, 255); text-decoration-style: initial; text-decoration-color: initial;">This PCB can withstand roughly 10W ERP - which is 3 Watts more than any of my HT's can output. Plenty of breathing room + Gain.</p>
<p style="margin: 0px; padding: 0px; cursor: text; box-sizing: border-box; counter-reset: list-1 0 list-2 0 list-3 0 list-4 0 list-5 0 list-6 0 list-7 0 list-8 0 list-9 0; color: rgb(49, 49, 49); font-family: Helvetica, Arial, sans-serif; font-size: 13px; font-style: normal; font-variant-ligatures: normal; font-variant-caps: normal; font-weight: 400; letter-spacing: normal; orphans: 2; text-align: left; text-indent: 0px; text-transform: none; white-space: pre-wrap; widows: 2; word-spacing: 0px; -webkit-text-stroke-width: 0px; background-color: rgb(255, 255, 255); text-decoration-style: initial; text-decoration-color: initial;">
  <br style="box-sizing: border-box;">
</p>
<p style="margin: 0px; padding: 0px; cursor: text; box-sizing: border-box; counter-reset: list-1 0 list-2 0 list-3 0 list-4 0 list-5 0 list-6 0 list-7 0 list-8 0 list-9 0; color: rgb(49, 49, 49); font-family: Helvetica, Arial, sans-serif; font-size: 13px; font-style: normal; font-variant-ligatures: normal; font-variant-caps: normal; font-weight: 400; letter-spacing: normal; orphans: 2; text-align: left; text-indent: 0px; text-transform: none; white-space: pre-wrap; widows: 2; word-spacing: 0px; -webkit-text-stroke-width: 0px; background-color: rgb(255, 255, 255); text-decoration-style: initial; text-decoration-color: initial;">
  
</p>
<p style="margin: 0px; padding: 0px; cursor: text; box-sizing: border-box; counter-reset: list-1 0 list-2 0 list-3 0 list-4 0 list-5 0 list-6 0 list-7 0 list-8 0 list-9 0; color: rgb(49, 49, 49); font-family: Helvetica, Arial, sans-serif; font-size: 13px; font-style: normal; font-variant-ligatures: normal; font-variant-caps: normal; font-weight: 400; letter-spacing: normal; orphans: 2; text-align: left; text-indent: 0px; text-transform: none; white-space: pre-wrap; widows: 2; word-spacing: 0px; -webkit-text-stroke-width: 0px; background-color: rgb(255, 255, 255); text-decoration-style: initial; text-decoration-color: initial;">
  <br style="box-sizing: border-box;">
</p>
<h3 style="margin: 0px; padding: 0px; cursor: text; box-sizing: border-box; counter-reset: list-1 0 list-2 0 list-3 0 list-4 0 list-5 0 list-6 0 list-7 0 list-8 0 list-9 0; font-size: 1.17em; color: rgb(49, 49, 49); font-family: Helvetica, Arial, sans-serif; font-style: normal; font-variant-ligatures: normal; font-variant-caps: normal; letter-spacing: normal; orphans: 2; text-align: left; text-indent: 0px; text-transform: none; white-space: pre-wrap; widows: 2; word-spacing: 0px; -webkit-text-stroke-width: 0px; background-color: rgb(255, 255, 255); text-decoration-style: initial; text-decoration-color: initial;">Topside</h3>
<p style="margin: 0px; padding: 0px; cursor: text; box-sizing: border-box; counter-reset: list-1 0 list-2 0 list-3 0 list-4 0 list-5 0 list-6 0 list-7 0 list-8 0 list-9 0; color: rgb(49, 49, 49); font-family: Helvetica, Arial, sans-serif; font-size: 13px; font-style: normal; font-variant-ligatures: normal; font-variant-caps: normal; font-weight: 400; letter-spacing: normal; orphans: 2; text-align: left; text-indent: 0px; text-transform: none; white-space: pre-wrap; widows: 2; word-spacing: 0px; -webkit-text-stroke-width: 0px; background-color: rgb(255, 255, 255); text-decoration-style: initial; text-decoration-color: initial;">
  <br style="box-sizing: border-box;">
</p>
<p style="margin: 0px; padding: 0px; cursor: text; box-sizing: border-box; counter-reset: list-1 0 list-2 0 list-3 0 list-4 0 list-5 0 list-6 0 list-7 0 list-8 0 list-9 0; color: rgb(49, 49, 49); font-family: Helvetica, Arial, sans-serif; font-size: 13px; font-style: normal; font-variant-ligatures: normal; font-variant-caps: normal; font-weight: 400; letter-spacing: normal; orphans: 2; text-align: left; text-indent: 0px; text-transform: none; white-space: pre-wrap; widows: 2; word-spacing: 0px; -webkit-text-stroke-width: 0px; background-color: rgb(255, 255, 255); text-decoration-style: initial; text-decoration-color: initial;">
  
</p>
<p style="margin: 0px; padding: 0px; cursor: text; box-sizing: border-box; counter-reset: list-1 0 list-2 0 list-3 0 list-4 0 list-5 0 list-6 0 list-7 0 list-8 0 list-9 0; color: rgb(49, 49, 49); font-family: Helvetica, Arial, sans-serif; font-size: 13px; font-style: normal; font-variant-ligatures: normal; font-variant-caps: normal; font-weight: 400; letter-spacing: normal; orphans: 2; text-align: left; text-indent: 0px; text-transform: none; white-space: pre-wrap; widows: 2; word-spacing: 0px; -webkit-text-stroke-width: 0px; background-color: rgb(255, 255, 255); text-decoration-style: initial; text-decoration-color: initial;">
  <br style="box-sizing: border-box;">
</p>
<h3 style="margin: 0px; padding: 0px; cursor: text; box-sizing: border-box; counter-reset: list-1 0 list-2 0 list-3 0 list-4 0 list-5 0 list-6 0 list-7 0 list-8 0 list-9 0; font-size: 1.17em; color: rgb(49, 49, 49); font-family: Helvetica, Arial, sans-serif; font-style: normal; font-variant-ligatures: normal; font-variant-caps: normal; letter-spacing: normal; orphans: 2; text-align: left; text-indent: 0px; text-transform: none; white-space: pre-wrap; widows: 2; word-spacing: 0px; -webkit-text-stroke-width: 0px; background-color: rgb(255, 255, 255); text-decoration-style: initial; text-decoration-color: initial;">Rearside</h3>
<p style="margin: 0px; padding: 0px; cursor: text; box-sizing: border-box; counter-reset: list-1 0 list-2 0 list-3 0 list-4 0 list-5 0 list-6 0 list-7 0 list-8 0 list-9 0; color: rgb(49, 49, 49); font-family: Helvetica, Arial, sans-serif; font-size: 13px; font-style: normal; font-variant-ligatures: normal; font-variant-caps: normal; font-weight: 400; letter-spacing: normal; orphans: 2; text-align: left; text-indent: 0px; text-transform: none; white-space: pre-wrap; widows: 2; word-spacing: 0px; -webkit-text-stroke-width: 0px; background-color: rgb(255, 255, 255); text-decoration-style: initial; text-decoration-color: initial;">
  <br style="box-sizing: border-box;">
</p>
<p style="margin: 0px; padding: 0px; cursor: text; box-sizing: border-box; counter-reset: list-1 0 list-2 0 list-3 0 list-4 0 list-5 0 list-6 0 list-7 0 list-8 0 list-9 0; color: rgb(49, 49, 49); font-family: Helvetica, Arial, sans-serif; font-size: 13px; font-style: normal; font-variant-ligatures: normal; font-variant-caps: normal; font-weight: 400; letter-spacing: normal; orphans: 2; text-align: left; text-indent: 0px; text-transform: none; white-space: pre-wrap; widows: 2; word-spacing: 0px; -webkit-text-stroke-width: 0px; background-color: rgb(255, 255, 255); text-decoration-style: initial; text-decoration-color: initial;">
  
</p>
<p style="margin: 0px; padding: 0px; cursor: text; box-sizing: border-box; counter-reset: list-1 0 list-2 0 list-3 0 list-4 0 list-5 0 list-6 0 list-7 0 list-8 0 list-9 0; color: rgb(49, 49, 49); font-family: Helvetica, Arial, sans-serif; font-size: 13px; font-style: normal; font-variant-ligatures: normal; font-variant-caps: normal; font-weight: 400; letter-spacing: normal; orphans: 2; text-align: left; text-indent: 0px; text-transform: none; white-space: pre-wrap; widows: 2; word-spacing: 0px; -webkit-text-stroke-width: 0px; background-color: rgb(255, 255, 255); text-decoration-style: initial; text-decoration-color: initial;">
  <br style="box-sizing: border-box;">
</p>
<h2 style="margin: 0px; padding: 0px; cursor: text; box-sizing: border-box; counter-reset: list-1 0 list-2 0 list-3 0 list-4 0 list-5 0 list-6 0 list-7 0 list-8 0 list-9 0; font-size: 1.5em; color: rgb(49, 49, 49); font-family: Helvetica, Arial, sans-serif; font-style: normal; font-variant-ligatures: normal; font-variant-caps: normal; letter-spacing: normal; orphans: 2; text-align: left; text-indent: 0px; text-transform: none; white-space: pre-wrap; widows: 2; word-spacing: 0px; -webkit-text-stroke-width: 0px; background-color: rgb(255, 255, 255); text-decoration-style: initial; text-decoration-color: initial;">Wiring Diagram</h2>
<p style="margin: 0px; padding: 0px; cursor: text; box-sizing: border-box; counter-reset: list-1 0 list-2 0 list-3 0 list-4 0 list-5 0 list-6 0 list-7 0 list-8 0 list-9 0; color: rgb(49, 49, 49); font-family: Helvetica, Arial, sans-serif; font-size: 13px; font-style: normal; font-variant-ligatures: normal; font-variant-caps: normal; font-weight: 400; letter-spacing: normal; orphans: 2; text-align: left; text-indent: 0px; text-transform: none; white-space: pre-wrap; widows: 2; word-spacing: 0px; -webkit-text-stroke-width: 0px; background-color: rgb(255, 255, 255); text-decoration-style: initial; text-decoration-color: initial;">
  <br style="box-sizing: border-box;">
</p>
<p style="margin: 0px; padding: 0px; cursor: text; box-sizing: border-box; counter-reset: list-1 0 list-2 0 list-3 0 list-4 0 list-5 0 list-6 0 list-7 0 list-8 0 list-9 0; color: rgb(49, 49, 49); font-family: Helvetica, Arial, sans-serif; font-size: 13px; font-style: normal; font-variant-ligatures: normal; font-variant-caps: normal; font-weight: 400; letter-spacing: normal; orphans: 2; text-align: left; text-indent: 0px; text-transform: none; white-space: pre-wrap; widows: 2; word-spacing: 0px; -webkit-text-stroke-width: 0px; background-color: rgb(255, 255, 255); text-decoration-style: initial; text-decoration-color: initial;">
  
</p>
<p style="margin: 0px; padding: 0px; cursor: text; box-sizing: border-box; counter-reset: list-1 0 list-2 0 list-3 0 list-4 0 list-5 0 list-6 0 list-7 0 list-8 0 list-9 0; color: rgb(49, 49, 49); font-family: Helvetica, Arial, sans-serif; font-size: 13px; font-style: normal; font-variant-ligatures: normal; font-variant-caps: normal; font-weight: 400; letter-spacing: normal; orphans: 2; text-align: left; text-indent: 0px; text-transform: none; white-space: pre-wrap; widows: 2; word-spacing: 0px; -webkit-text-stroke-width: 0px; background-color: rgb(255, 255, 255); text-decoration-style: initial; text-decoration-color: initial;">
  <br style="box-sizing: border-box;">
</p>
<p style="margin: 0px; padding: 0px; cursor: text; box-sizing: border-box; counter-reset: list-1 0 list-2 0 list-3 0 list-4 0 list-5 0 list-6 0 list-7 0 list-8 0 list-9 0; color: rgb(49, 49, 49); font-family: Helvetica, Arial, sans-serif; font-size: 13px; font-style: normal; font-variant-ligatures: normal; font-variant-caps: normal; font-weight: 400; letter-spacing: normal; orphans: 2; text-align: left; text-indent: 0px; text-transform: none; white-space: pre-wrap; widows: 2; word-spacing: 0px; -webkit-text-stroke-width: 0px; background-color: rgb(255, 255, 255); text-decoration-style: initial; text-decoration-color: initial;">Thank you very much for bearing with this. I would like to shout out the team at PCB Way for supporting me in developing and printing my project. If you want to see more :) - 
  <a href="https://github.com/AxiomYT/Electronic-Design/tree/70CM%2C-2M-Diplexer" style="text-decoration: underline; color: rgb(0, 102, 204); transition: color 0.25s ease-out 0s; box-sizing: border-box;" target="_blank">https://github.com/AxiomYT/Electronic-Design/tree/70CM%2C-2M-Diplexer</a>
</p>
<p style="margin: 0px; padding: 0px; cursor: text; box-sizing: border-box; counter-reset: list-1 0 list-2 0 list-3 0 list-4 0 list-5 0 list-6 0 list-7 0 list-8 0 list-9 0; color: rgb(49, 49, 49); font-family: Helvetica, Arial, sans-serif; font-size: 13px; font-style: normal; font-variant-ligatures: normal; font-variant-caps: normal; font-weight: 400; letter-spacing: normal; orphans: 2; text-align: left; text-indent: 0px; text-transform: none; white-space: pre-wrap; widows: 2; word-spacing: 0px; -webkit-text-stroke-width: 0px; background-color: rgb(255, 255, 255); text-decoration-style: initial; text-decoration-color: initial;">
  <br style="box-sizing: border-box;">
</p>
<p style="margin: 0px; padding: 0px; cursor: text; box-sizing: border-box; counter-reset: list-1 0 list-2 0 list-3 0 list-4 0 list-5 0 list-6 0 list-7 0 list-8 0 list-9 0; color: rgb(49, 49, 49); font-family: Helvetica, Arial, sans-serif; font-size: 13px; font-style: normal; font-variant-ligatures: normal; font-variant-caps: normal; font-weight: 400; letter-spacing: normal; orphans: 2; text-align: left; text-indent: 0px; text-transform: none; white-space: pre-wrap; widows: 2; word-spacing: 0px; -webkit-text-stroke-width: 0px; background-color: rgb(255, 255, 255); text-decoration-style: initial; text-decoration-color: initial;">Follow me on Github :) - 
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
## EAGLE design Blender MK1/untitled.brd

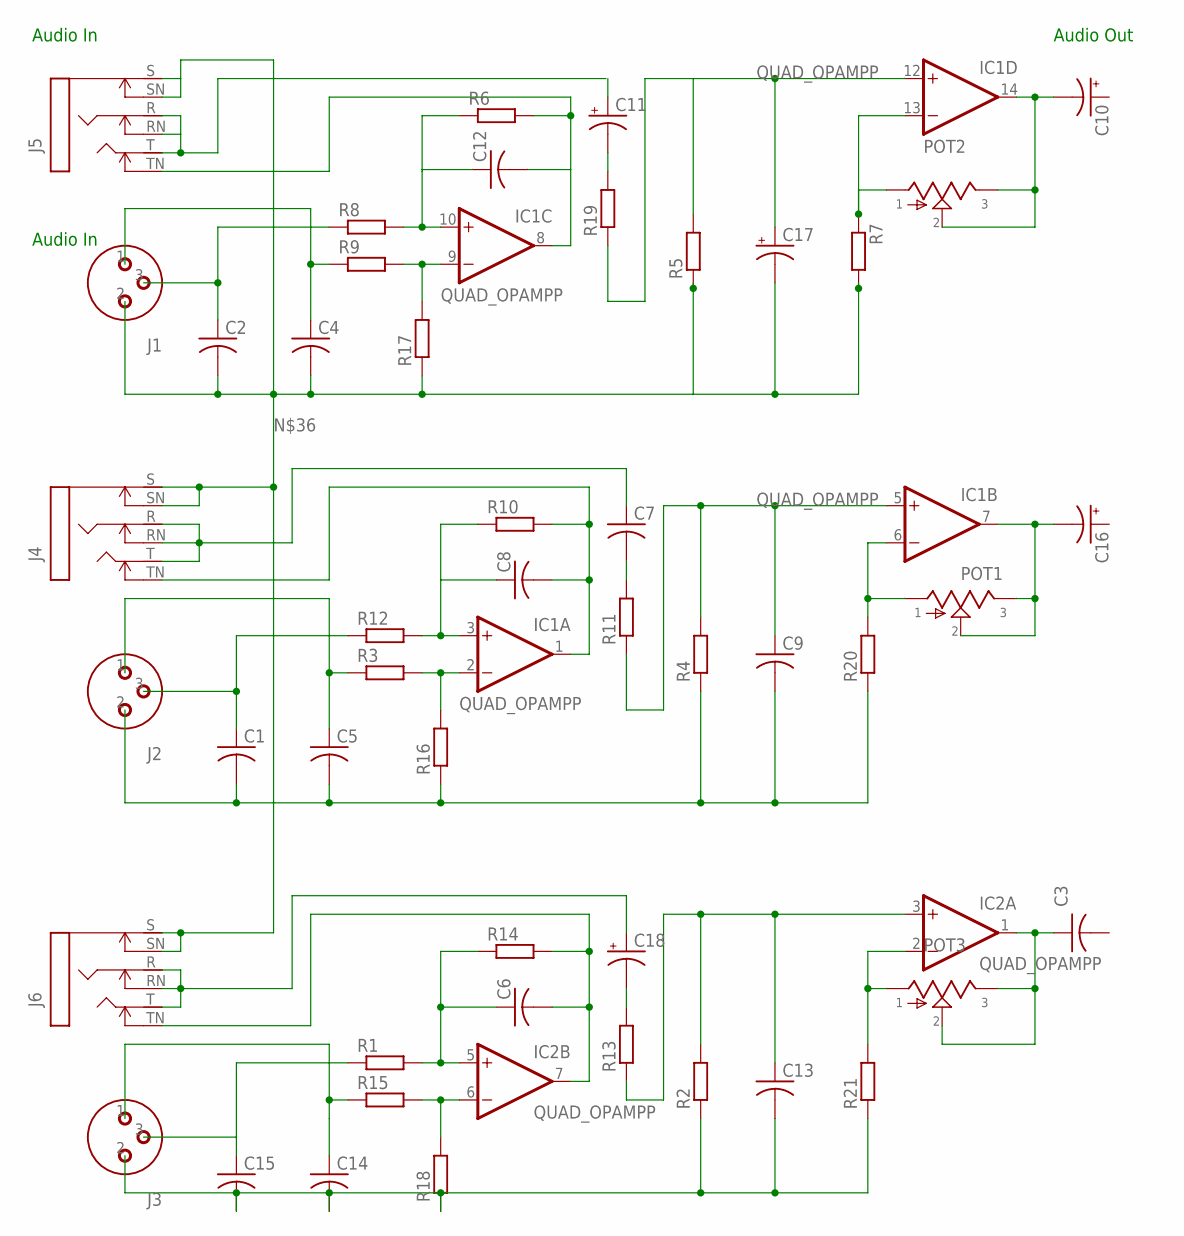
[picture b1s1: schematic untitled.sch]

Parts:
C1, C2, C3, C4, C5, C6, C7, C8, C9, C12, C13, C14, C15: C-US025-030X050; C025-030X050
C10, C11, C16, C17, C18: CPOL-USE1.8-4; E1,8-4
IC1, IC2: QUAD_OPAMPP; DIL14
J1, J2, J3: XLR; XLR_PADS
J4, J5, J6: STEREOSWS; NMJ6HC-S
POT1, POT2, POT3: POT
R1, R2, R3, R4, R5, R6, R7, R8, R9, R10, R11, R12, R13, R14, R15, R16, R17, R18, R19, R20, R21: R-EU_0204/7; 0204/7

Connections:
unnamed: C17.+, IC1.12 (+IN), R5.2, R19.1
unnamed: C13.2, C14.2, C15.2, J3.2, R2.1, R18.1, R21.1
unnamed: J5.R, J5.RN, J5.T
unnamed: C12.1, IC1.10 (+IN), R6.1, R8.2
unnamed: IC1.9 (-IN), R9.2, R17.2
unnamed: C11.-, R19.2
unnamed: IC1.13 (-IN), POT2.1, R7.1
unnamed: C10.-, IC1.14 (OUT), POT2.2, POT2.3
unnamed: C4.1, J1.1, R9.1
unnamed: C2.1, J1.3, R8.1
unnamed: C7.1, J4.R, J4.RN, J4.T
unnamed: C1.2, C5.2, C9.2, J2.2, R4.1, R16.1, R20.1
unnamed: C12.2, IC1.8 (OUT), J5.TN, R6.2
unnamed: IC1.2 (-IN), R3.2, R16.2
unnamed: C5.1, J2.1, R3.1
unnamed: C1.1, J2.3, R12.1
unnamed: C8.1, IC1.3 (+IN), R10.1, R12.2
unnamed: C7.2, R11.2
unnamed: C18.+, J6.R, J6.RN, J6.T
unnamed: C8.2, IC1.1 (OUT), J4.TN, R10.2
unnamed: C9.1, IC1.5 (+IN), R4.2, R11.1
unnamed: IC1.6 (-IN), POT1.1, R20.2
unnamed: C16.-, IC1.7 (OUT), POT1.2, POT1.3
unnamed: IC2.2 (-IN), POT3.1, R21.2
unnamed: C3.1, IC2.1 (OUT), POT3.2, POT3.3
unnamed: C6.1, IC2.5 (+IN), R1.2, R14.1
unnamed: IC2.6 (-IN), R15.2, R18.2
unnamed: C15.1, J3.3, R1.1
unnamed: C14.1, J3.1, R15.1
unnamed: C6.2, IC2.7 (OUT), J6.TN, R14.2
unnamed: C18.-, R13.2
unnamed: C13.1, IC2.3 (+IN), R2.2, R13.1
unnamed: C2.2, C4.2, C17.-, J1.2, J4.S, J4.SN, J5.S, J5.SN, J6.S, J6.SN, R5.1, R7.2, R17.1
V+: IC1.4 (V+), IC2.4 (V+)
V-: IC1.11 (V-), IC2.11 (V-)

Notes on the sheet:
Audio In
Audio Out

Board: 2 copper layers, 50 parts (0 on the bottom side), 35 nets, no tracks yet.

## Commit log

2019-10-07 Create 3D Printed Case
2019-10-07 Create adsads
2019-10-07 Create asd
2019-10-07 Create sefsfe
2019-10-07 Create sefggsdg
2021-12-31 This is temporary file storage (for now)
    Happy new years :)
